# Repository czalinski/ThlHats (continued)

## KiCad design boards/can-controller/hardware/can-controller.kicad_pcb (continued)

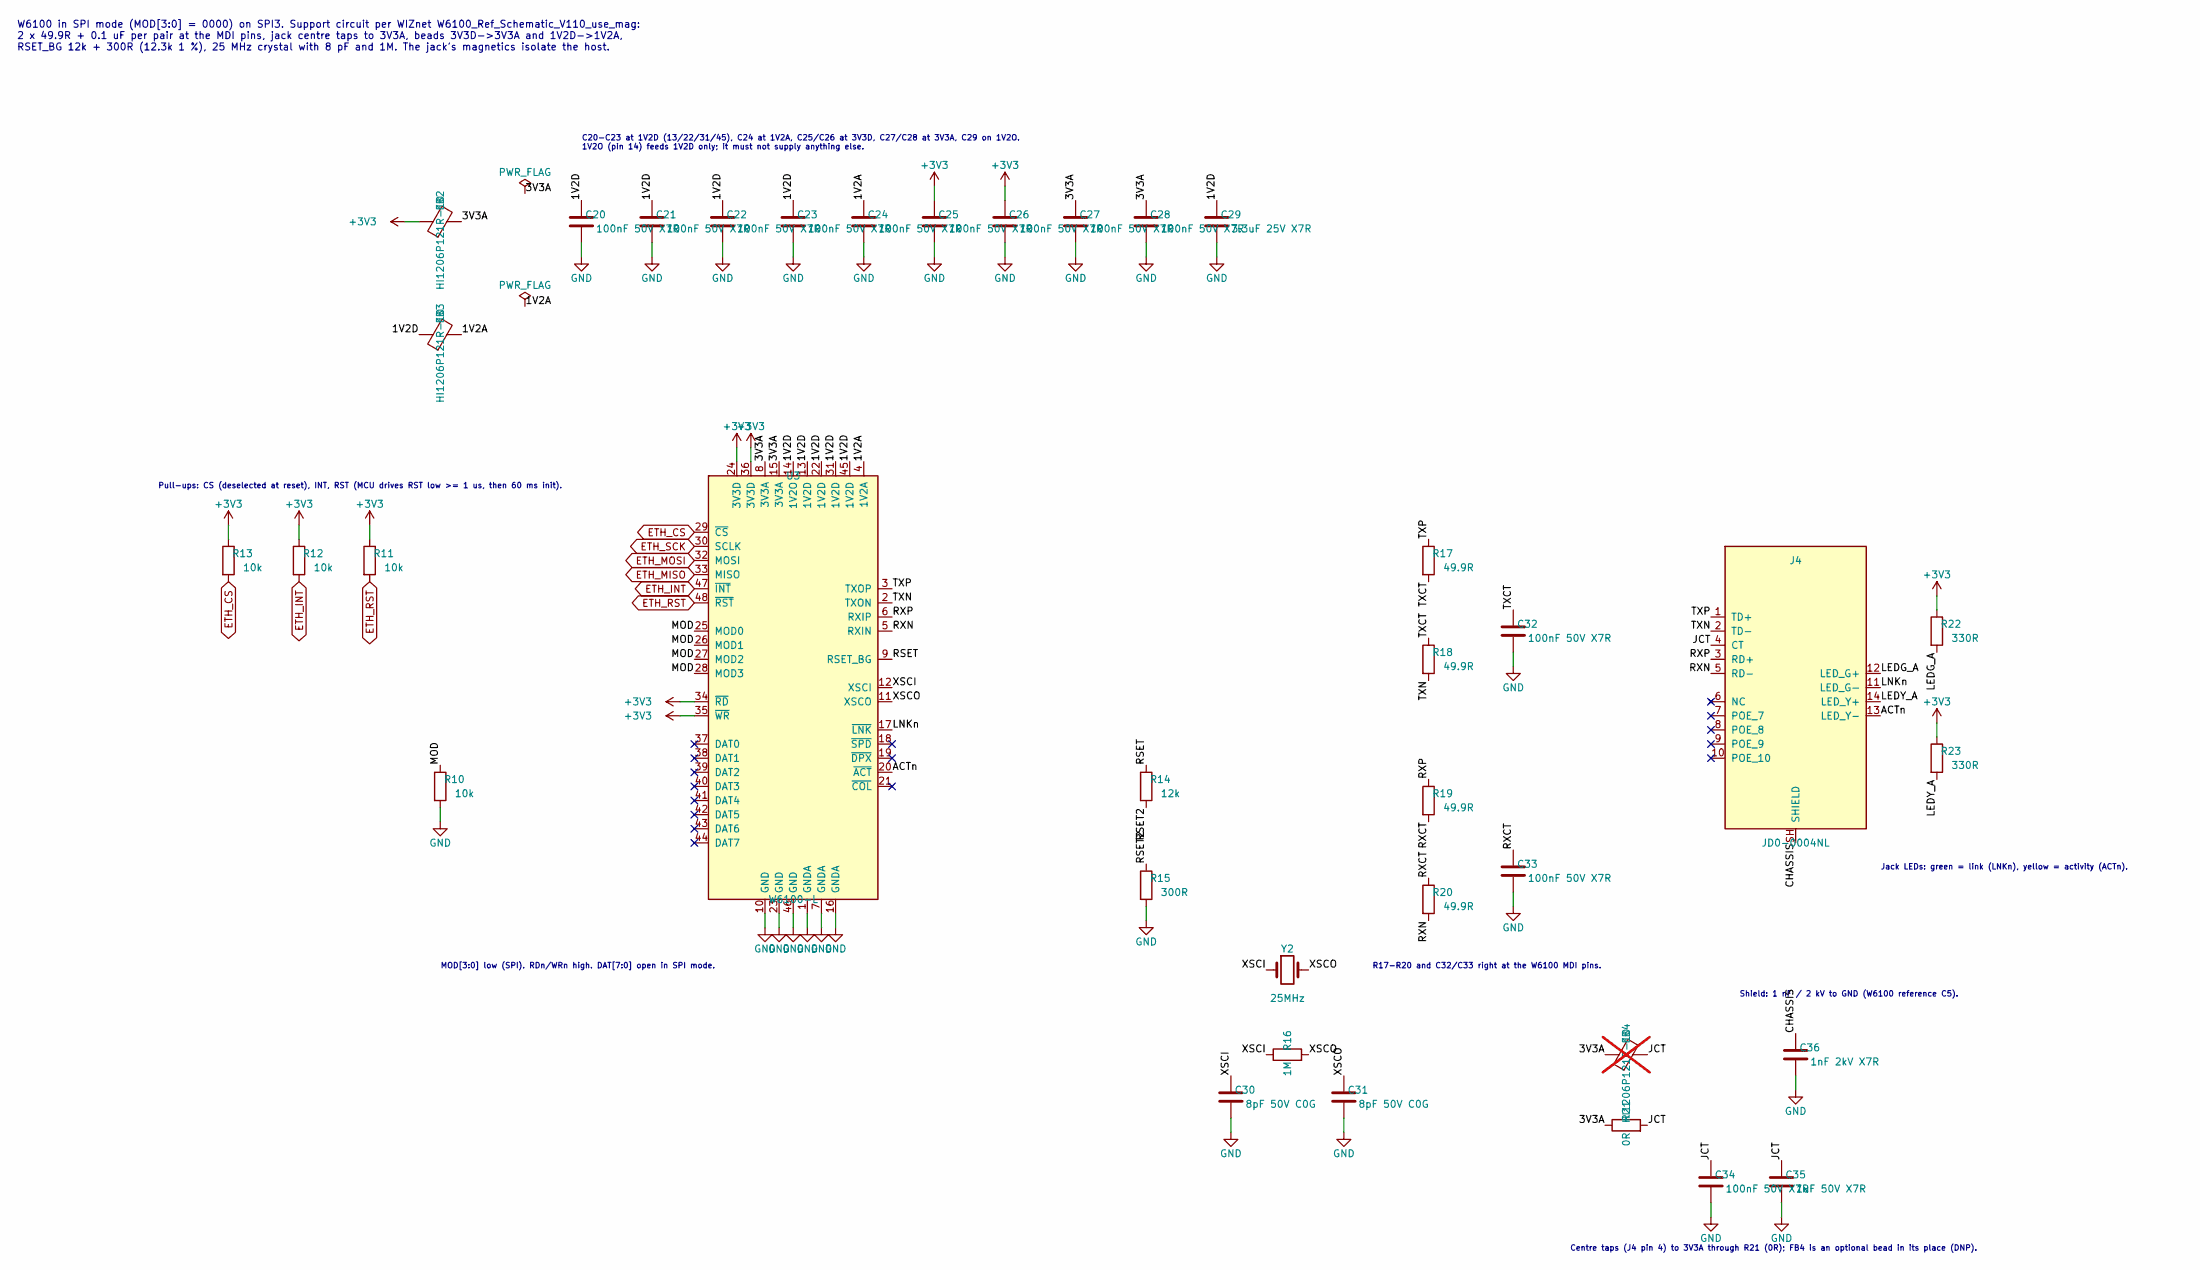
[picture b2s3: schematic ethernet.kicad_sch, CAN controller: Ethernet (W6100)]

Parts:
C20, C21, C22, C23, C24, C25, C26, C27, C28, C32, C33, C34: 100nF 50V X7R; C_0805_2012Metric_Pad1.18x1.45mm_HandSolder; MPN C0805C104K5RACTU
C29: 3.3uF 25V X7R; C_1206_3216Metric_Pad1.33x1.80mm_HandSolder; MPN TBD (3.3 uF 25 V X7R 1206)
C30, C31: 8pF 50V C0G; C_0805_2012Metric_Pad1.18x1.45mm_HandSolder; MPN TBD (8 pF 50 V C0G 0805, to suit the 25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
C35: 1uF 50V X7R; C_1206_3216Metric_Pad1.33x1.80mm_HandSolder; MPN C1206C105K5RACTU
C36: 1nF 2kV X7R; C_1206_3216Metric_Pad1.33x1.80mm_HandSolder; MPN C1206C102KGRACTU
FB2, FB3: HI1206P121R-10; L_1206_3216Metric_Pad1.22x1.90mm_HandSolder; MPN HI1206P121R-10
FB4: HI1206P121R-10; L_1206_3216Metric_Pad1.22x1.90mm_HandSolder; MPN HI1206P121R-10; not fitted
J4: JD0-0004NL; RJ45_Pulse_JD0-0004NL_Horizontal; MPN JD0-0004NL
R10, R11, R12, R13: 10k; R_1206_3216Metric_Pad1.30x1.75mm_HandSolder; MPN RC1206FR-0710KL
R14: 12k; R_1206_3216Metric_Pad1.30x1.75mm_HandSolder; MPN RC1206FR-0712KL
R15: 300R; R_1206_3216Metric_Pad1.30x1.75mm_HandSolder; MPN RC1206FR-07300RL
R16: 1M; R_1206_3216Metric_Pad1.30x1.75mm_HandSolder; MPN RC1206FR-071ML
R17, R18, R19, R20: 49.9R; R_1206_3216Metric_Pad1.30x1.75mm_HandSolder; MPN RC1206FR-0749R9L
R21: 0R; R_1206_3216Metric_Pad1.30x1.75mm_HandSolder; MPN RC1206JR-070RL
R22, R23: 330R; R_1206_3216Metric_Pad1.30x1.75mm_HandSolder; MPN RMCF1206FT330R
U3: W6100-L; LQFP-48_7x7mm_P0.5mm; MPN W6100-L
Y2: 25MHz; Crystal_SMD_5032-2Pin_5.0x3.2mm_HandSoldering; MPN TBD (25 MHz, 5032, CL 12 pF)

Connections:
+3V3: C25.1, C26.1, FB2.1, R11.1, R12.1, R13.1, R22.1, R23.1, U3.24 (3V3D), U3.34 (~RD), U3.35 (~WR), U3.36 (3V3D); also elsewhere on the board
/Ethernet/1V2A: C24.1, FB3.2, U3.4 (1V2A)
/Ethernet/1V2D: C20.1, C21.1, C22.1, C23.1, C29.1, FB3.1, U3.13 (1V2D), U3.14 (1V2O), U3.22 (1V2D), U3.31 (1V2D), U3.45 (1V2D)
/Ethernet/3V3A: C27.1, C28.1, FB2.2, FB4.1, R21.1, U3.8 (3V3A), U3.15 (3V3A)
/Ethernet/ACTn: J4.13 (LED_Y-), U3.20 (~ACT)
/Ethernet/CHASSIS: C36.1, J4.SH (SHIELD)
/Ethernet/JCT: C34.1, C35.1, FB4.2, J4.4 (CT), R21.2
/Ethernet/LEDG_A: J4.12 (LED_G+), R22.2
/Ethernet/LEDY_A: J4.14 (LED_Y+), R23.2
/Ethernet/LNKn: J4.11 (LED_G-), U3.17 (~LNK)
/Ethernet/MOD: R10.1, U3.25 (MOD0), U3.26 (MOD1), U3.27 (MOD2), U3.28 (MOD3)
/Ethernet/RSET: R14.1, U3.9 (RSET_BG)
/Ethernet/RSET2: R14.2, R15.1
/Ethernet/RXCT: C33.1, R19.2, R20.1
/Ethernet/RXN: J4.5 (RD-), R20.2, U3.5 (RXIN)
/Ethernet/RXP: J4.3 (RD+), R19.1, U3.6 (RXIP)
/Ethernet/TXCT: C32.1, R17.2, R18.1
/Ethernet/TXN: J4.2 (TD-), R18.2, U3.2 (TXON)
/Ethernet/TXP: J4.1 (TD+), R17.1, U3.3 (TXOP)
/Ethernet/XSCI: C30.1, R16.1, U3.12 (XSCI), Y2.1
/Ethernet/XSCO: C31.1, R16.2, U3.11 (XSCO), Y2.2
ETH_CS: R13.2, U3.29 (~CS); also elsewhere on the board
ETH_INT: R12.2, U3.47 (~INT); also elsewhere on the board
ETH_MISO: U3.33 (MISO); also elsewhere on the board
ETH_MOSI: U3.32 (MOSI); also elsewhere on the board
ETH_RST: R11.2, U3.48 (~RST); also elsewhere on the board
ETH_SCK: U3.30 (SCLK); also elsewhere on the board
GND: C20.2, C21.2, C22.2, C23.2, C24.2, C25.2, C26.2, C27.2, C28.2, C29.2, C30.2, C31.2, C32.2, C33.2, C34.2, C35.2, C36.2, R10.2, R15.2, U3.1 (GNDA), U3.7 (GNDA), U3.10 (GND), U3.16 (GNDA), U3.23 (GND), U3.46 (GND); also elsewhere on the board

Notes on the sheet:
W6100 in SPI mode (MOD[3:0] = 0000) on SPI3. Support circuit per WIZnet W6100_Ref_Schematic_V110_use_mag: 2 x 49.9R + 0.1 uF per pair at the MDI pins, jack centre taps to 3V3A, beads 3V3D->3V3A and 1V2D->1V2A, RSET_BG 12k + 300R (12.3k 1 %), 25 MHz crystal with 8 pF and 1M. The jack's magnetics iso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
MOD[3:0] low (SPI). RDn/WRn high. DAT[7:0] open in SPI mode.
Pull-ups: CS (deselected at reset), INT, RST (MCU drives RST low >= 1 us, then 60 ms init).
C20-C23 at 1V2D (13/22/31/45), C24 at 1V2A, C25/C26 at 3V3D, C27/C28 at 3V3A, C29 on 1V2O. 1V2O (pin 14) feeds 1V2D only; it must not supply anything else.
R17-R20 and C32/C33 right at the W6100 MDI pins.
Centre taps (J4 pin 4) to 3V3A through R21 (0R); FB4 is an optional bead in its place (DNP).
Jack LEDs: green = link (LNKn), yellow = activity (ACTn).
Shield: 1 nF / 2 kV to GND (W6100 reference C5).

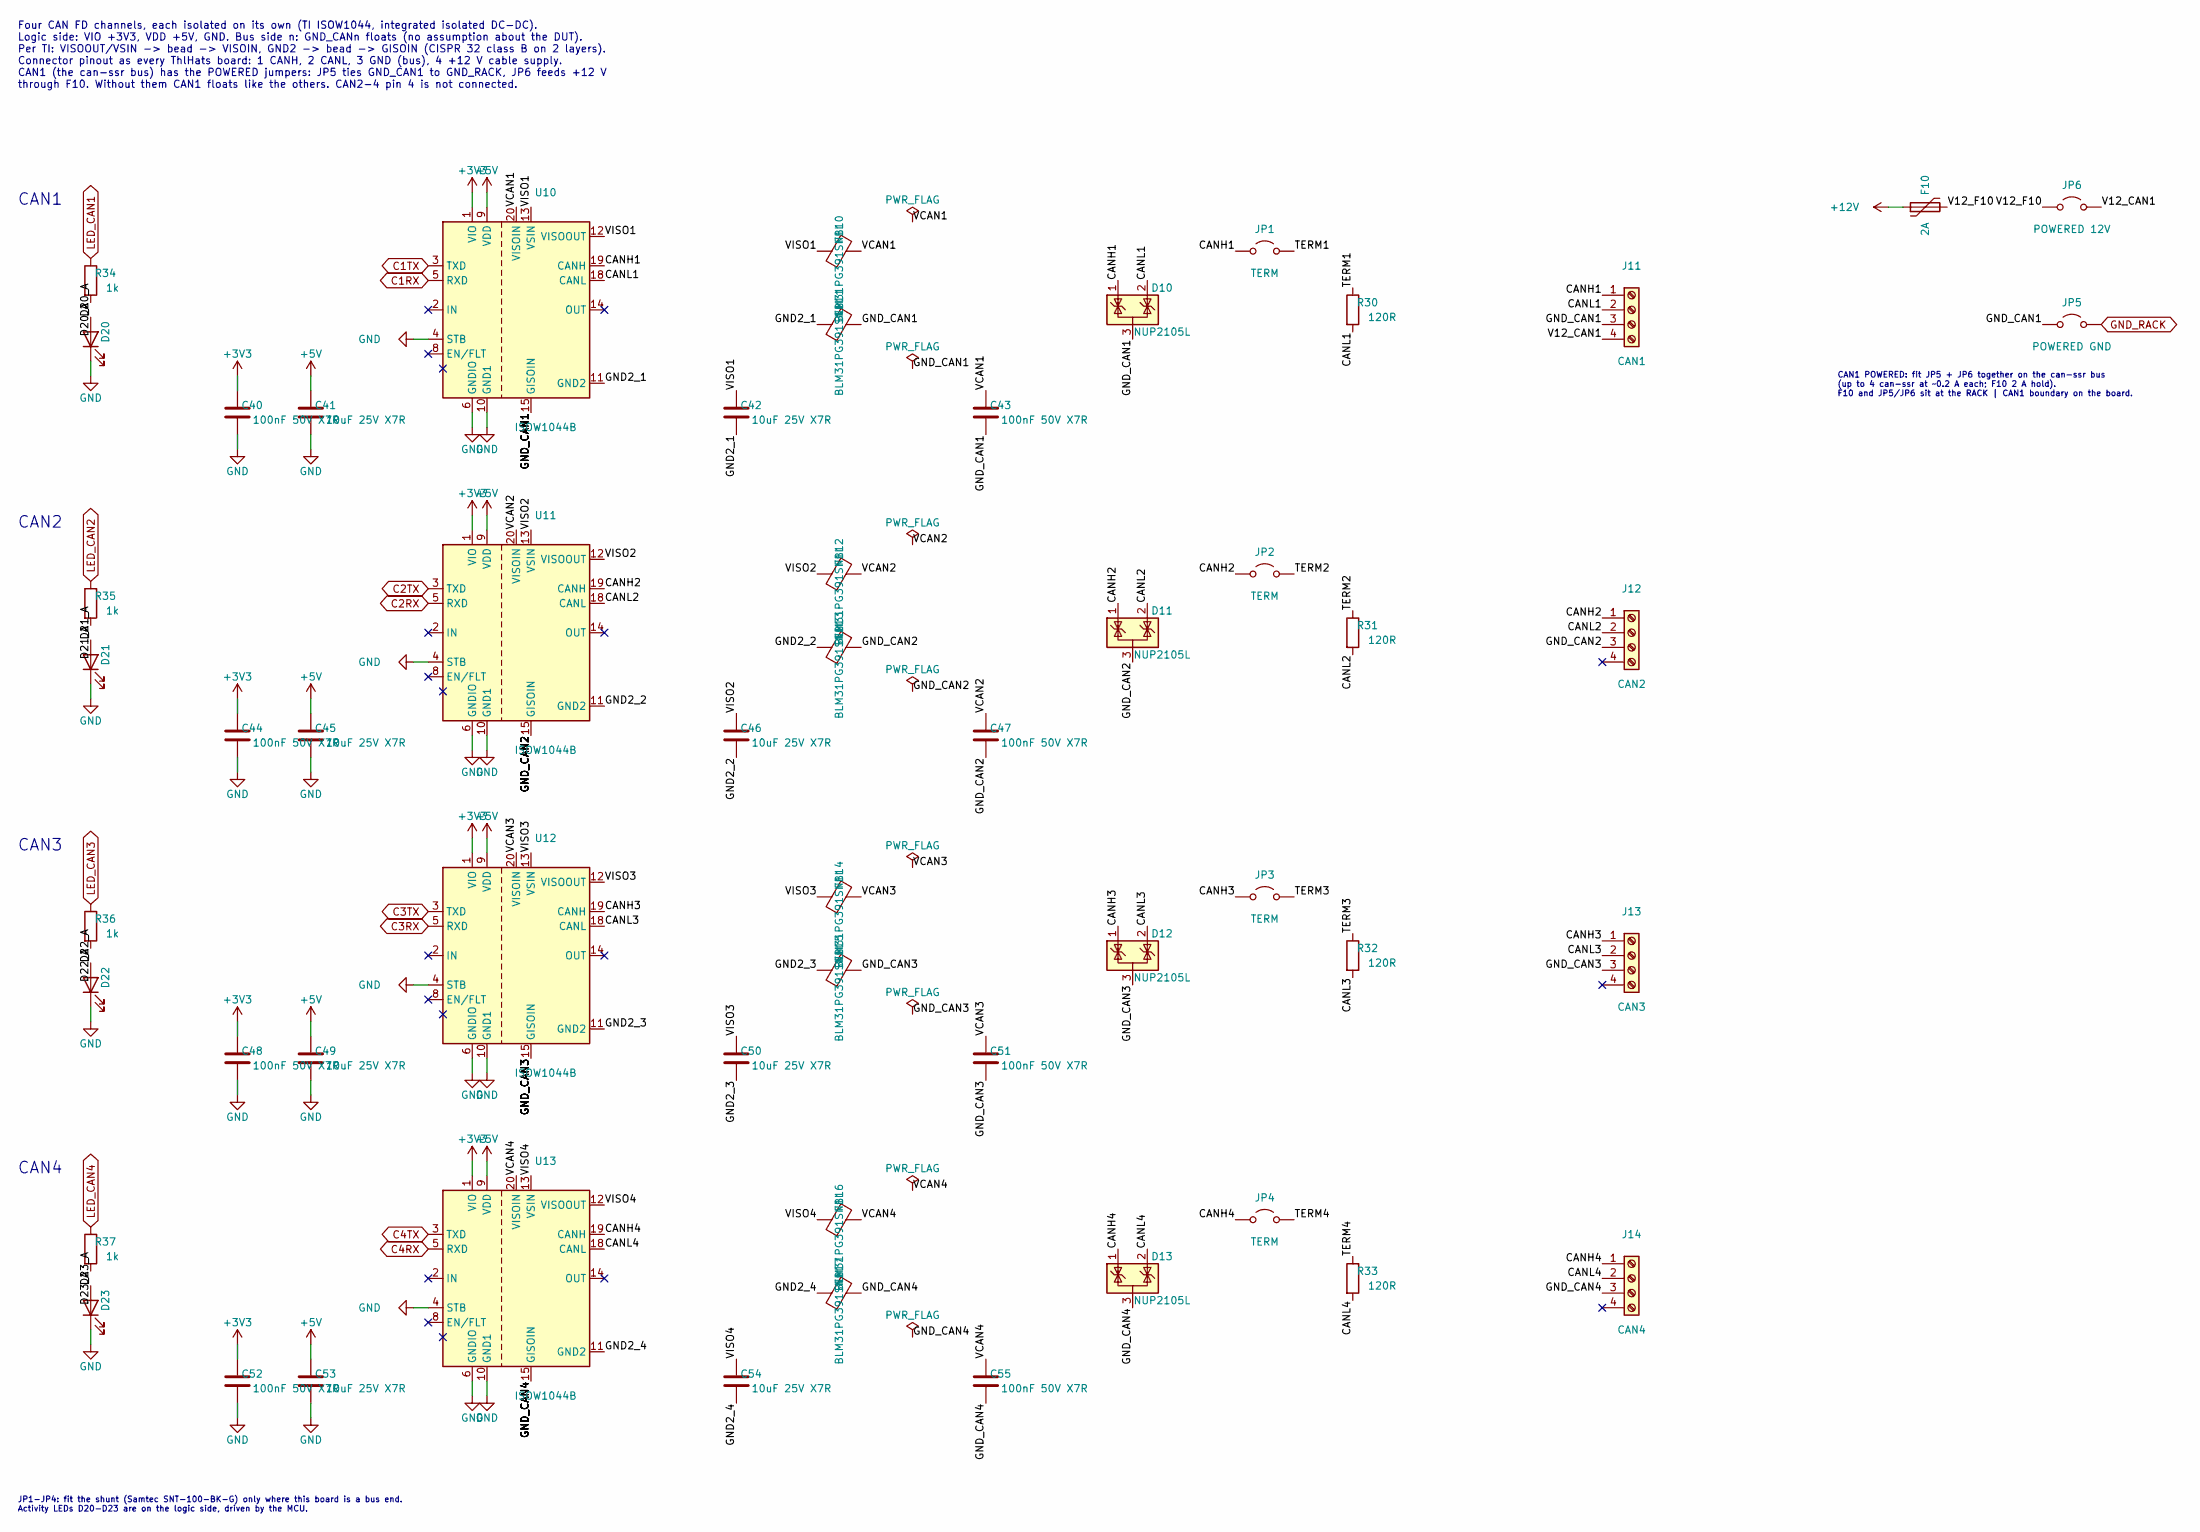
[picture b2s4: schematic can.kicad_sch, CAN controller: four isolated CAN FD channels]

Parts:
C40, C43, C44, C47, C48, C51, C52, C55: 100nF 50V X7R; C_0805_2012Metric_Pad1.18x1.45mm_HandSolder; MPN C0805C104K5RACTU
C41, C42, C45, C46, C49, C50, C53, C54: 10uF 25V X7R; C_1206_3216Metric_Pad1.33x1.80mm_HandSolder; MPN CL31B106KAHZW6E
D10, D11, D12, D13: NUP2105L; SOT-23; MPN NUP2105LT1G
D20, D21, D22, D23: LED yellow; LED_1206_3216Metric_Pad1.42x1.75mm_HandSolder; MPN LTST-C150YKT
F10: 2A; Fuse_1812_4532Metric_Pad1.30x3.40mm_HandSolder; MPN MF-MSMF200/16X-2
FB10, FB11, FB12, FB13, FB14, FB15, FB16, FB17: BLM31PG391SN1L; L_1206_3216Metric_Pad1.22x1.90mm_HandSolder; MPN BLM31PG391SN1L
J11: CAN1; PhoenixContact_MC_1,5_4-G-3.5_1x04_P3.50mm_Horizontal; MPN 1844236
J12: CAN2; PhoenixContact_MC_1,5_4-G-3.5_1x04_P3.50mm_Horizontal; MPN 1844236
J13: CAN3; PhoenixContact_MC_1,5_4-G-3.5_1x04_P3.50mm_Horizontal; MPN 1844236
J14: CAN4; PhoenixContact_MC_1,5_4-G-3.5_1x04_P3.50mm_Horizontal; MPN 1844236
JP1, JP2, JP3, JP4: TERM; PinHeader_1x02_P2.54mm_Vertical; MPN TSW-102-07-G-S
JP5: POWERED GND; PinHeader_1x02_P2.54mm_Vertical; MPN TSW-102-07-G-S
JP6: POWERED 12V; PinHeader_1x02_P2.54mm_Vertical; MPN TSW-102-07-G-S
R30, R31, R32, R33: 120R; R_1206_3216Metric_Pad1.30x1.75mm_HandSolder; MPN RC1206FR-07120RL
R34, R35, R36, R37: 1k; R_1206_3216Metric_Pad1.30x1.75mm_HandSolder; MPN RC1206FR-071KL
U10, U11, U12, U13: ISOW1044B; SOIC-20W_7.5x12.8mm_P1.27mm; MPN ISOW1044BDFMR

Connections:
+3V3: C40.1, C44.1, C48.1, C52.1, U10.1 (VIO), U11.1 (VIO), U12.1 (VIO), U13.1 (VIO); also elsewhere on the board
+5V: C41.1, C45.1, C49.1, C53.1, U10.9 (VDD), U11.9 (VDD), U12.9 (VDD), U13.9 (VDD); also elsewhere on the board
+12V: F10.1; also elsewhere on the board
/CAN x4/CANH1: D10.1 (K), J11.1, JP1.1 (A), U10.19 (CANH)
/CAN x4/CANH2: D11.1 (K), J12.1, JP2.1 (A), U11.19 (CANH)
/CAN x4/CANH3: D12.1 (K), J13.1, JP3.1 (A), U12.19 (CANH)
/CAN x4/CANH4: D13.1 (K), J14.1, JP4.1 (A), U13.19 (CANH)
/CAN x4/CANL1: D10.2 (K), J11.2, R30.2, U10.18 (CANL)
/CAN x4/CANL2: D11.2 (K), J12.2, R31.2, U11.18 (CANL)
/CAN x4/CANL3: D12.2 (K), J13.2, R32.2, U12.18 (CANL)
/CAN x4/CANL4: D13.2 (K), J14.2, R33.2, U13.18 (CANL)
/CAN x4/D20_A: D20.2 (A), R34.2
/CAN x4/D21_A: D21.2 (A), R35.2
/CAN x4/D22_A: D22.2 (A), R36.2
/CAN x4/D23_A: D23.2 (A), R37.2
/CAN x4/GND2_1: C42.2, FB11.1, U10.11 (GND2)
/CAN x4/GND2_2: C46.2, FB13.1, U11.11 (GND2)
/CAN x4/GND2_3: C50.2, FB15.1, U12.11 (GND2)
/CAN x4/GND2_4: C54.2, FB17.1, U13.11 (GND2)
/CAN x4/GND_CAN1: C43.2, D10.3 (A), FB11.2, J11.3, JP5.1 (A), U10.15 (GISOIN), U10.16 (GISOIN), U10.17 (GISOIN)
/CAN x4/GND_CAN2: C47.2, D11.3 (A), FB13.2, J12.3, U11.15 (GISOIN), U11.16 (GISOIN), U11.17 (GISOIN)
/CAN x4/GND_CAN3: C51.2, D12.3 (A), FB15.2, J13.3, U12.15 (GISOIN), U12.16 (GISOIN), U12.17 (GISOIN)
/CAN x4/GND_CAN4: C55.2, D13.3 (A), FB17.2, J14.3, U13.15 (GISOIN), U13.16 (GISOIN), U13.17 (GISOIN)
/CAN x4/TERM1: JP1.2 (B), R30.1
/CAN x4/TERM2: JP2.2 (B), R31.1
/CAN x4/TERM3: JP3.2 (B), R32.1
/CAN x4/TERM4: JP4.2 (B), R33.1
/CAN x4/V12_CAN1: J11.4, JP6.2 (B)
/CAN x4/V12_F10: F10.2, JP6.1 (A)
/CAN x4/VCAN1: C43.1, FB10.2, U10.20 (VISOIN)
/CAN x4/VCAN2: C47.1, FB12.2, U11.20 (VISOIN)
/CAN x4/VCAN3: C51.1, FB14.2, U12.20 (VISOIN)
/CAN x4/VCAN4: C55.1, FB16.2, U13.20 (VISOIN)
/CAN x4/VISO1: C42.1, FB10.1, U10.12 (VISOOUT), U10.13 (VSIN)
/CAN x4/VISO2: C46.1, FB12.1, U11.12 (VISOOUT), U11.13 (VSIN)
/CAN x4/VISO3: C50.1, FB14.1, U12.12 (VISOOUT), U12.13 (VSIN)
/CAN x4/VISO4: C54.1, FB16.1, U13.12 (VISOOUT), U13.13 (VSIN)
C1RX: U10.5 (RXD); also elsewhere on the board
C1TX: U10.3 (TXD); also elsewhere on the board
C2RX: U11.5 (RXD); also elsewhere on the board
C2TX: U11.3 (TXD); also elsewhere on the board
C3RX: U12.5 (RXD); also elsewhere on the board
C3TX: U12.3 (TXD); also elsewhere on the board
C4RX: U13.5 (RXD); also elsewhere on the board
C4TX: U13.3 (TXD); also elsewhere on the board
GND: C40.2, C41.2, C44.2, C45.2, C48.2, C49.2, C52.2, C53.2, D20.1 (K), D21.1 (K), D22.1 (K), D23.1 (K), U10.4 (STB), U10.6 (GNDIO), U10.10 (GND1), U11.4 (STB), U11.6 (GNDIO), U11.10 (GND1), U12.4 (STB), U12.6 (GNDIO), U12.10 (GND1), U13.4 (STB), U13.6 (GNDIO), U13.10 (GND1); also elsewhere on the board
GND_RACK: JP5.2 (B); also elsewhere on the board
LED_CAN1: R34.1; also elsewhere on the board
LED_CAN2: R35.1; also elsewhere on the board
LED_CAN3: R36.1; also elsewhere on the board
LED_CAN4: R37.1; also elsewhere on the board

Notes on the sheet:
Four CAN FD channels, each isolated on its own (TI ISOW1044, integrated isolated DC-DC). Logic side: VIO +3V3, VDD +5V, GND. Bus side n: GND_CANn floats (no assumption about the DUT). Per TI: VISOOUT/VSIN -> bead -> VISOIN, GND2 -> bead -> GISOIN (CISPR 32 class B on 2 layers). Connector pinout as 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
CAN1
CAN2
CAN3
CAN4
CAN1 POWERED: fit JP5 + JP6 together on the can-ssr bus (up to 4 can-ssr at ~0.2 A each; F10 2 A hold). F10 and JP5/JP6 sit at the RACK | CAN1 boundary on the board.
JP1-JP4: fit the shunt (Samtec SNT-100-BK-G) only where this board is a bus end. Activity LEDs D20-D23 are on the logic side, driven by the MCU.

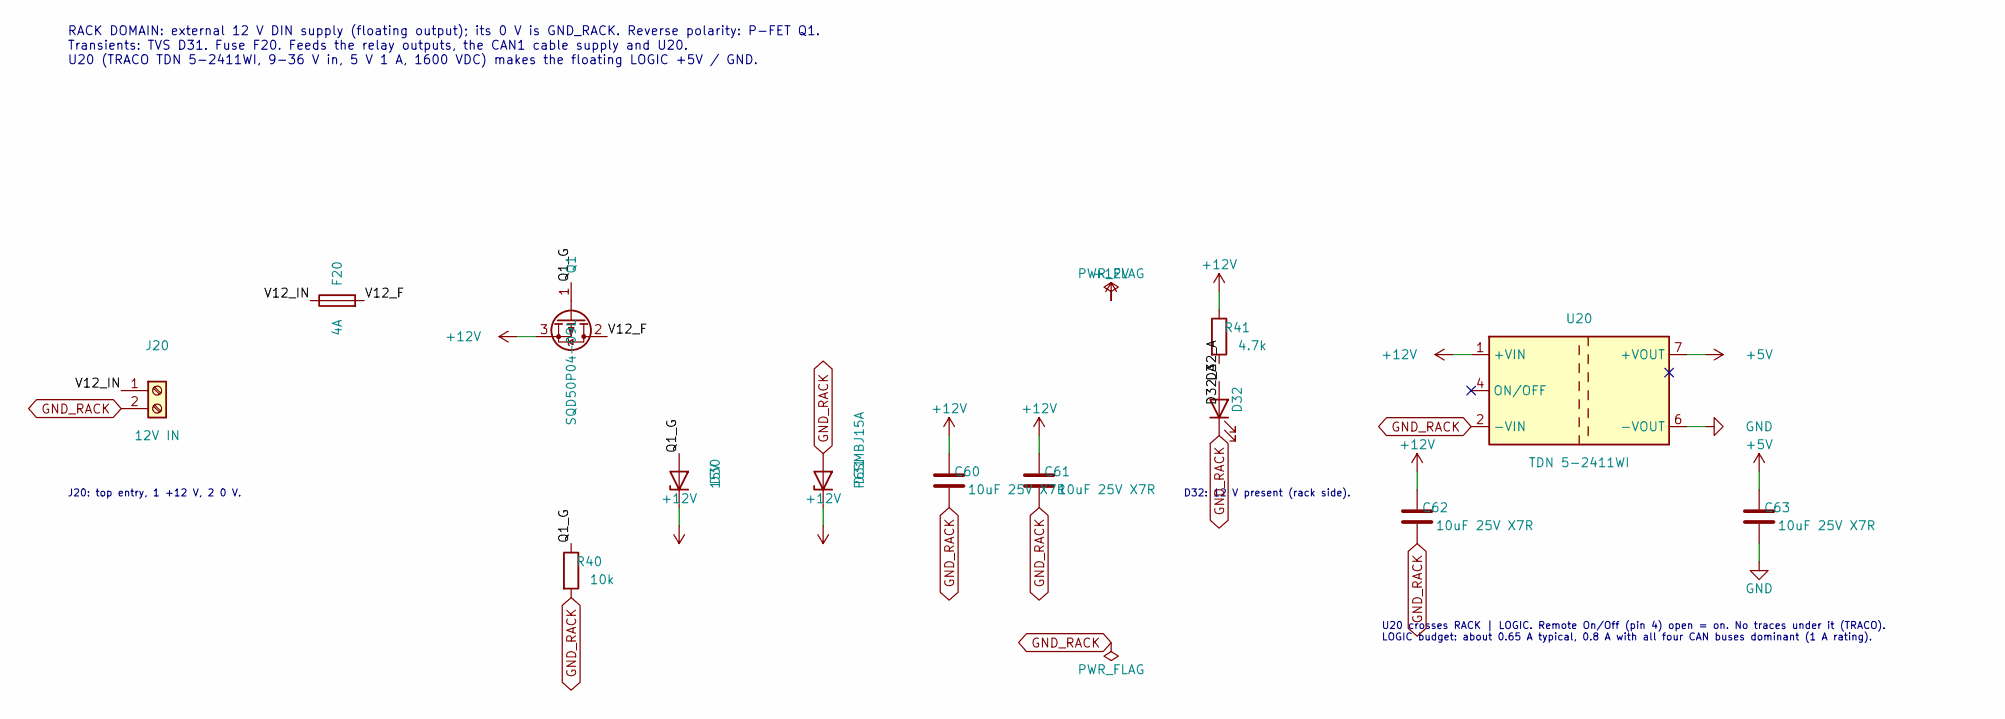
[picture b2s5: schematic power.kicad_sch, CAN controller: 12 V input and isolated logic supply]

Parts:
C60, C61, C62, C63: 10uF 25V X7R; C_1206_3216Metric_Pad1.33x1.80mm_HandSolder; MPN CL31B106KAHZW6E
D30: 15V; D_SOD-123; MPN BZT52C15-7-F
D31: P6SMBJ15A; D_SMB_Handsoldering; MPN P6SMBJ15A
D32: LED green; LED_1206_3216Metric_Pad1.42x1.75mm_HandSolder; MPN LTST-C150KGKT
F20: 4A; Fuse_Littelfuse-NANO2-451_453; MPN 0451004.MRL
J20: 12V IN; PhoenixContact_MSTBVA_2,5_2-G-5,08_1x02_P5.08mm_Vertical; MPN 1755736
Q1: SQD50P04-09L; TO-252-2; MPN SQD50P04-09L_GE3
R40: 10k; R_1206_3216Metric_Pad1.30x1.75mm_HandSolder; MPN RC1206FR-0710KL
R41: 4.7k; R_1206_3216Metric_Pad1.30x1.75mm_HandSolder; MPN RC1206FR-074K7L
U20: TDN 5-2411WI; Converter_DCDC_TRACO_TDN_5-xxxxWI_THT; MPN TDN 5-2411WI

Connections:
+5V: C63.1, U20.7 (+VOUT); also elsewhere on the board
+12V: C60.1, C61.1, C62.1, D30.1 (K), D31.1 (K), Q1.3 (S), R41.1, U20.1 (+VIN); also elsewhere on the board
/12 V input, logic supply/D32_A: D32.2 (A), R41.2
/12 V input, logic supply/Q1_G: D30.2 (A), Q1.1 (G), R40.1
/12 V input, logic supply/V12_F: F20.2, Q1.2 (D)
/12 V input, logic supply/V12_IN: F20.1, J20.1
GND: C63.2, U20.6 (-VOUT); also elsewhere on the board
GND_RACK: C60.2, C61.2, C62.2, D31.2 (A), D32.1 (K), J20.2, R40.2, U20.2 (-VIN); also elsewhere on the board

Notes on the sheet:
RACK DOMAIN: external 12 V DIN supply (floating output); its 0 V is GND_RACK. Reverse polarity: P-FET Q1. Transients: TVS D31. Fuse F20. Feeds the relay outputs, the CAN1 cable supply and U20. U20 (TRACO TDN 5-2411WI, 9-36 V in, 5 V 1 A, 1600 VDC) makes the floating LOGIC +5V / GND.
J20: top entry, 1 +12 V, 2 0 V.
D32: 12 V present (rack side).
U20 crosses RACK | LOGIC. Remote On/Off (pin 4) open = on. No traces under it (TRACO). LOGIC budget: about 0.65 A typical, 0.8 A with all four CAN buses dominant (1 A rating).

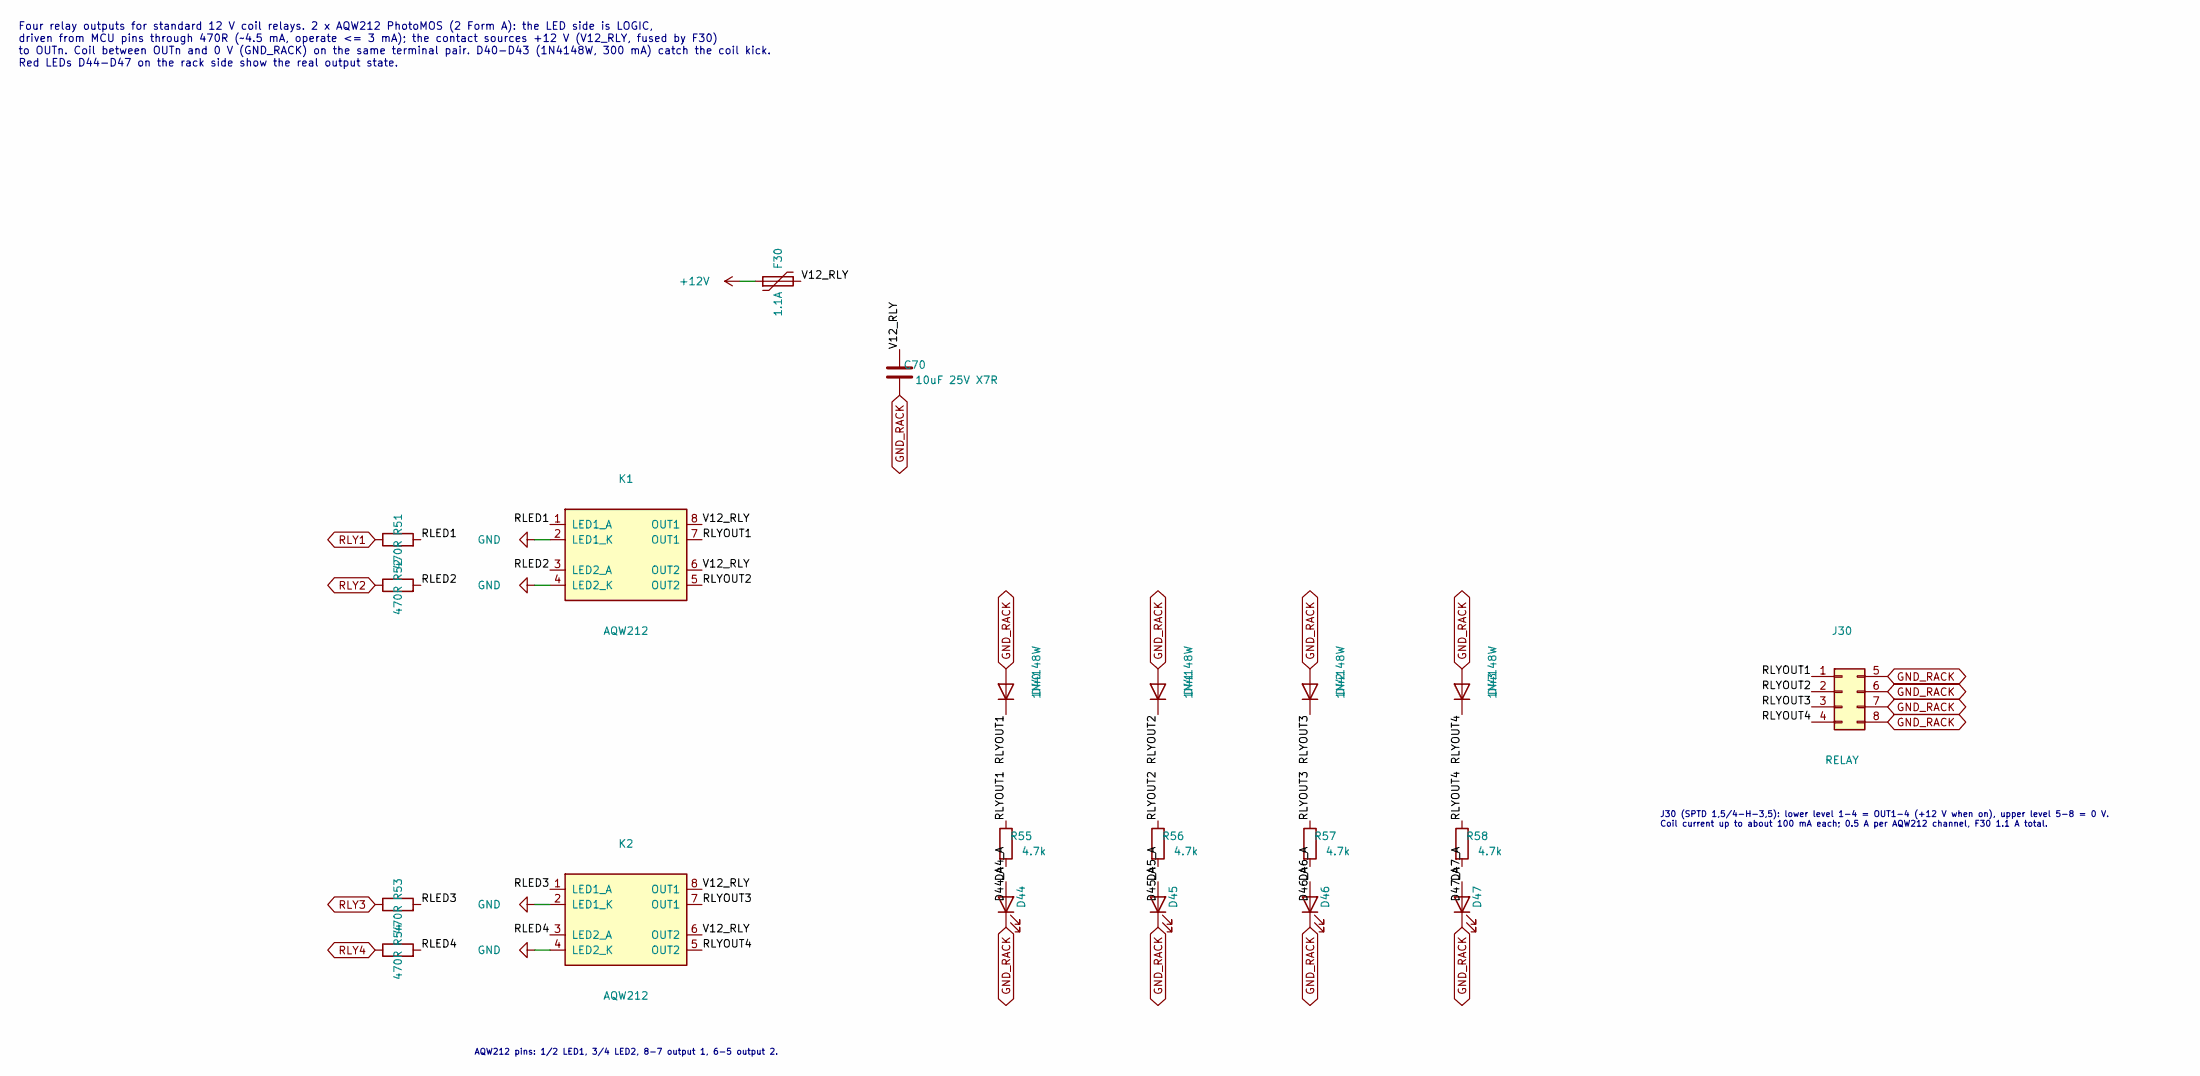
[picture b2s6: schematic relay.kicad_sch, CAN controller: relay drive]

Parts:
C70: 10uF 25V X7R; C_1206_3216Metric_Pad1.33x1.80mm_HandSolder; MPN CL31B106KAHZW6E
D40, D41, D42, D43: 1N4148W; D_SOD-123; MPN 1N4148W-7-F
D44, D45, D46, D47: LED red; LED_1206_3216Metric_Pad1.42x1.75mm_HandSolder; MPN LTST-C150KRKT
F30: 1.1A; Fuse_1812_4532Metric_Pad1.30x3.40mm_HandSolder; MPN 1812L110/16DR
J30: RELAY; PhoenixContact_SPTD_1,5_4-H-3,5_2x04_P3.5mm_Horizontal; MPN 1841513
K1, K2: AQW212; DIP-8_W7.62mm; MPN AQW212
R51, R52, R53, R54: 470R; R_1206_3216Metric_Pad1.30x1.75mm_HandSolder; MPN RC1206FR-07470RL
R55, R56, R57, R58: 4.7k; R_1206_3216Metric_Pad1.30x1.75mm_HandSolder; MPN RC1206FR-074K7L

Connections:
+12V: F30.1; also elsewhere on the board
/Relay drive/D44_A: D44.2 (A), R55.2
/Relay drive/D45_A: D45.2 (A), R56.2
/Relay drive/D46_A: D46.2 (A), R57.2
/Relay drive/D47_A: D47.2 (A), R58.2
/Relay drive/RLED1: K1.1 (LED1_A), R51.2
/Relay drive/RLED2: K1.3 (LED2_A), R52.2
/Relay drive/RLED3: K2.1 (LED1_A), R53.2
/Relay drive/RLED4: K2.3 (LED2_A), R54.2
/Relay drive/RLYOUT1: D40.1 (K), J30.1, K1.7 (OUT1), R55.1
/Relay drive/RLYOUT2: D41.1 (K), J30.2, K1.5 (OUT2), R56.1
/Relay drive/RLYOUT3: D42.1 (K), J30.3, K2.7 (OUT1), R57.1
/Relay drive/RLYOUT4: D43.1 (K), J30.4, K2.5 (OUT2), R58.1
/Relay drive/V12_RLY: C70.1, F30.2, K1.6 (OUT2), K1.8 (OUT1), K2.6 (OUT2), K2.8 (OUT1)
GND: K1.2 (LED1_K), K1.4 (LED2_K), K2.2 (LED1_K), K2.4 (LED2_K); also elsewhere on the board
GND_RACK: C70.2, D40.2 (A), D41.2 (A), D42.2 (A), D43.2 (A), D44.1 (K), D45.1 (K), D46.1 (K), D47.1 (K), J30.5, J30.6, J30.7, J30.8; also elsewhere on the board
RLY1: R51.1; also elsewhere on the board
RLY2: R52.1; also elsewhere on the board
RLY3: R53.1; also elsewhere on the board
RLY4: R54.1; also elsewhere on the board

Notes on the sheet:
Four relay outputs for standard 12 V coil relays. 2 x AQW212 PhotoMOS (2 Form A): the LED side is LOGIC, driven from MCU pins through 470R (~4.5 mA, operate <= 3 mA); the contact sources +12 V (V12_RLY, fused by F30) to OUTn. Coil between OUTn and 0 V (GND_RACK) on the same terminal pair. D40-D43 (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
AQW212 pins: 1/2 LED1, 3/4 LED2, 8-7 output 1, 6-5 output 2.
J30 (SPTD 1,5/4-H-3,5): lower level 1-4 = OUT1-4 (+12 V when on), upper level 5-8 = 0 V. Coil current up to about 100 mA each; 0.5 A per AQW212 channel, F30 1.1 A total.

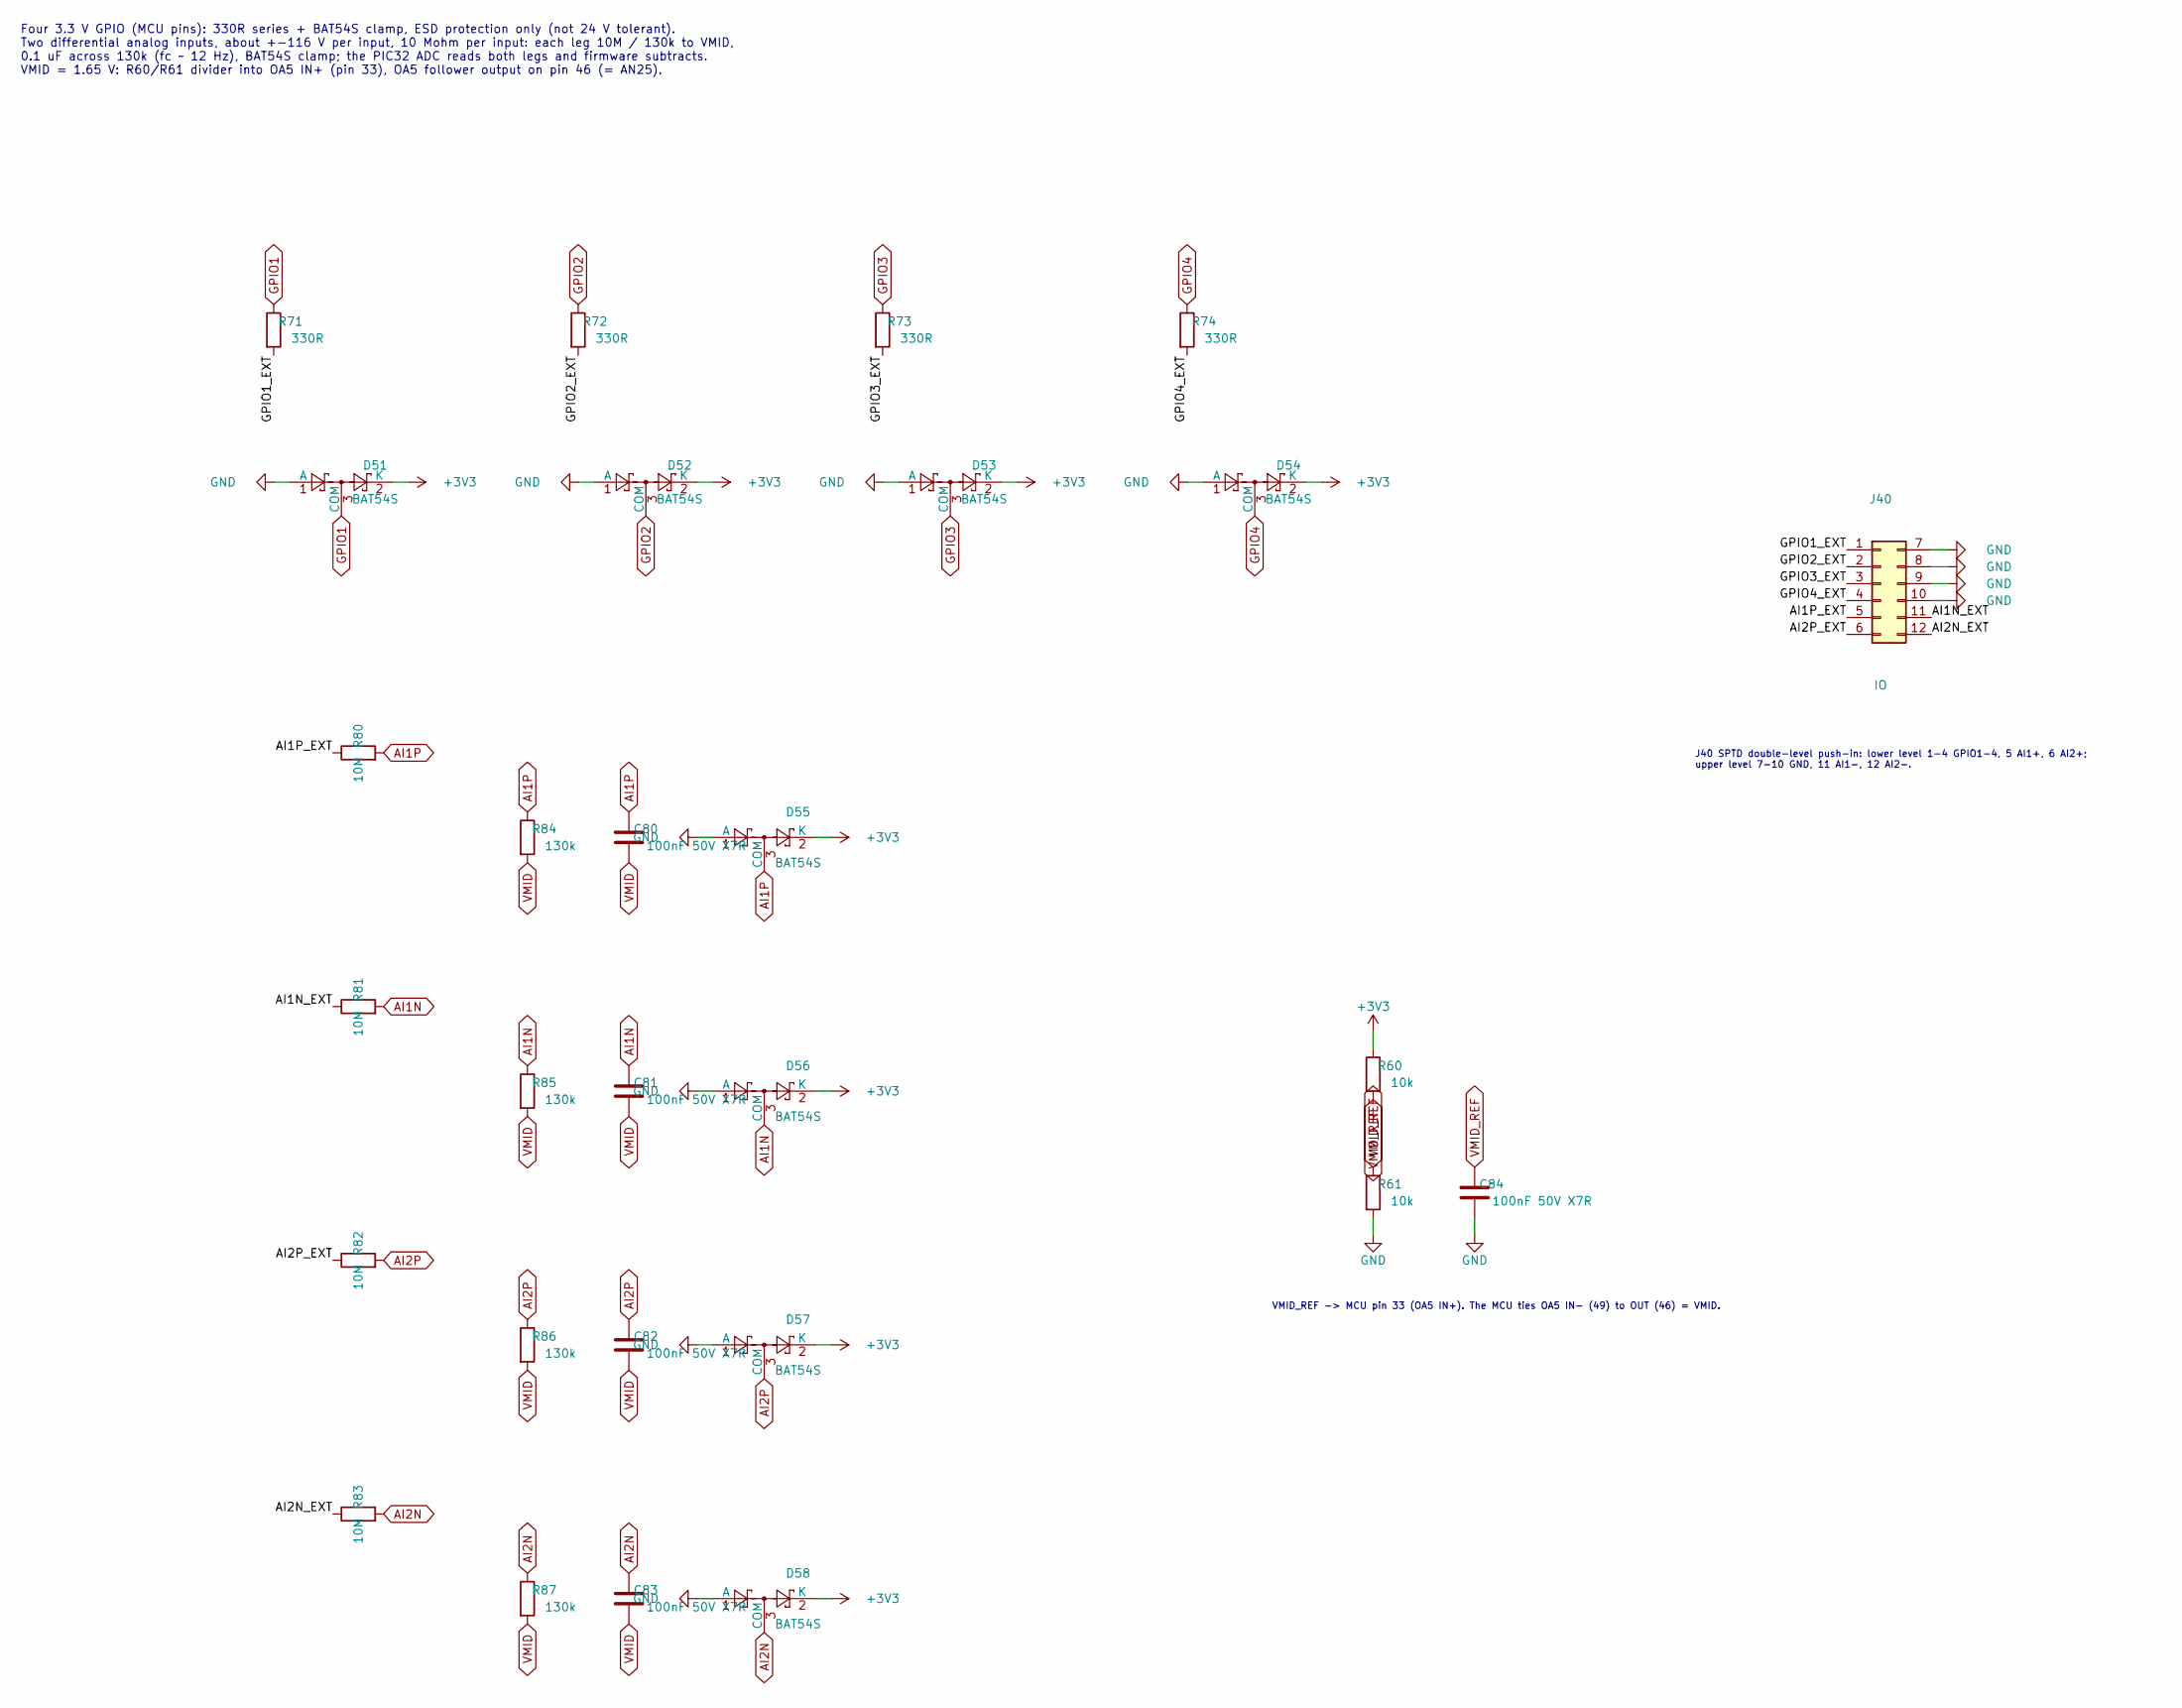
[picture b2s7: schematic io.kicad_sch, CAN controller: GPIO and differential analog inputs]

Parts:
C80, C81, C82, C83: 100nF 50V X7R; C_1206_3216Metric_Pad1.33x1.80mm_HandSolder; MPN C1206C104K5RACTU
C84: 100nF 50V X7R; C_0805_2012Metric_Pad1.18x1.45mm_HandSolder; MPN C0805C104K5RACTU
D51, D52, D53, D54, D55, D56, D57, D58: BAT54S; SOT-23; MPN BAT54S-7-F
J40: IO; PhoenixContact_SPTD_1,5_6-H-3,5_2x06_P3.5mm_Horizontal; MPN 1841539
R60, R61: 10k; R_1206_3216Metric_Pad1.30x1.75mm_HandSolder; MPN RC1206FR-0710KL
R71, R72, R73, R74: 330R; R_1206_3216Metric_Pad1.30x1.75mm_HandSolder; MPN RMCF1206FT330R
R80, R81, R82, R83: 10M; R_1206_3216Metric_Pad1.30x1.75mm_HandSolder; MPN RC1206FR-0710ML
R84, R85, R86, R87: 130k; R_1206_3216Metric_Pad1.30x1.75mm_HandSolder; MPN RC1206FR-07130KL

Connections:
+3V3: D51.2 (K), D52.2 (K), D53.2 (K), D54.2 (K), D55.2 (K), D56.2 (K), D57.2 (K), D58.2 (K), R60.1; also elsewhere on the board
/GPIO, analog in/AI1N_EXT: J40.11, R81.1
/GPIO, analog in/AI1P_EXT: J40.5, R80.1
/GPIO, analog in/AI2N_EXT: J40.12, R83.1
/GPIO, analog in/AI2P_EXT: J40.6, R82.1
/GPIO, analog in/GPIO1_EXT: J40.1, R71.2
/GPIO, analog in/GPIO2_EXT: J40.2, R72.2
/GPIO, analog in/GPIO3_EXT: J40.3, R73.2
/GPIO, analog in/GPIO4_EXT: J40.4, R74.2
AI1N: C81.1, D56.3 (COM), R81.2, R85.1; also elsewhere on the board
AI1P: C80.1, D55.3 (COM), R80.2, R84.1; also elsewhere on the board
AI2N: C83.1, D58.3 (COM), R83.2, R87.1; also elsewhere on the board
AI2P: C82.1, D57.3 (COM), R82.2, R86.1; also elsewhere on the board
GND: C84.2, D51.1 (A), D52.1 (A), D53.1 (A), D54.1 (A), D55.1 (A), D56.1 (A), D57.1 (A), D58.1 (A), J40.7, J40.8, J40.9, J40.10, R61.2; also elsewhere on the board
GPIO1: D51.3 (COM), R71.1; also elsewhere on the board
GPIO2: D52.3 (COM), R72.1; also elsewhere on the board
GPIO3: D53.3 (COM), R73.1; also elsewhere on the board
GPIO4: D54.3 (COM), R74.1; also elsewhere on the board
VMID: C80.2, C81.2, C82.2, C83.2, R84.2, R85.2, R86.2, R87.2; also elsewhere on the board
VMID_REF: C84.1, R60.2, R61.1; also elsewhere on the board

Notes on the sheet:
Four 3.3 V GPIO (MCU pins): 330R series + BAT54S clamp, ESD protection only (not 24 V tolerant). Two differential analog inputs, about +-116 V per input, 10 Mohm per input: each leg 10M / 130k to VMID, 0.1 uF across 130k (fc ~ 12 Hz), BAT54S clamp; the PIC32 ADC reads both legs and firmware subtrac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
J40 SPTD double-level push-in: lower level 1-4 GPIO1-4, 5 AI1+, 6 AI2+; upper level 7-10 GND, 11 AI1-, 12 AI2-.
VMID_REF -> MCU pin 33 (OA5 IN+). The MCU ties OA5 IN- (49) to OUT (46) = VMID.
